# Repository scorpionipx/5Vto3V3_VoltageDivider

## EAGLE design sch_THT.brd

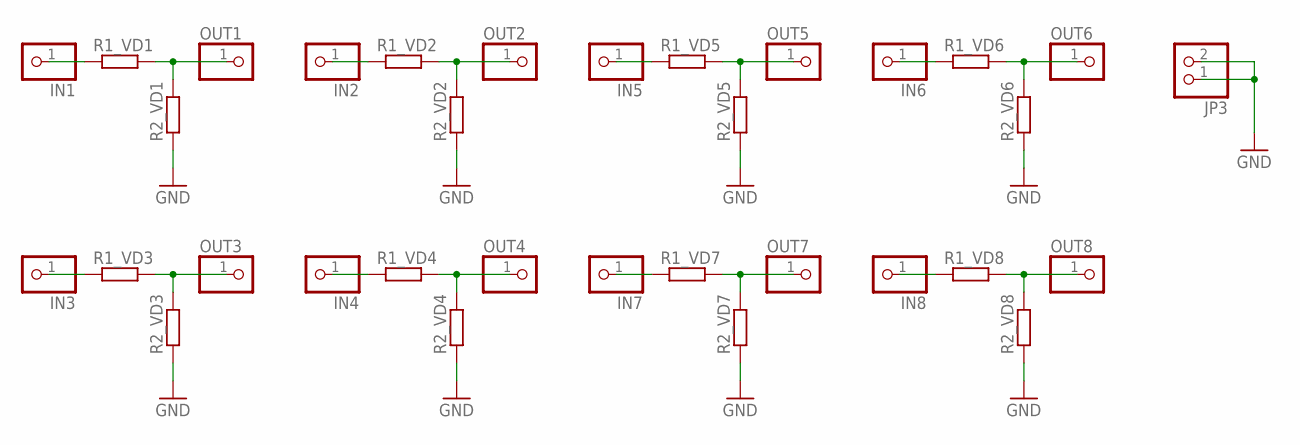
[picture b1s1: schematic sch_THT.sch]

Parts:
IN1, IN2, IN3, IN4, IN5, IN6, IN7, IN8: PINHD-1X1; 1X01
JP3: PINHD-1X2; 1X02
OUT1, OUT2, OUT3, OUT4, OUT5, OUT6, OUT7, OUT8: PINHD-1X1; 1X01
R1_VD1, R1_VD2, R1_VD3, R1_VD4, R1_VD5, R1_VD6, R1_VD7, R1_VD8, R2_VD1, R2_VD2, R2_VD3, R2_VD4, R2_VD5, R2_VD6, R2_VD7, R2_VD8: R-EU_0204/7; 0204/7

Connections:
GND: JP3.1, JP3.2, R2_VD1.1, R2_VD2.1, R2_VD3.1, R2_VD4.1, R2_VD5.1, R2_VD6.1, R2_VD7.1, R2_VD8.1
unnamed: IN1.1, R1_VD1.1
unnamed: OUT1.1, R1_VD1.2, R2_VD1.2
unnamed: IN2.1, R1_VD2.1
unnamed: OUT2.1, R1_VD2.2, R2_VD2.2
unnamed: IN3.1, R1_VD3.1
unnamed: OUT3.1, R1_VD3.2, R2_VD3.2
unnamed: IN4.1, R1_VD4.1
unnamed: OUT4.1, R1_VD4.2, R2_VD4.2
unnamed: IN5.1, R1_VD5.1
unnamed: OUT5.1, R1_VD5.2, R2_VD5.2
unnamed: IN6.1, R1_VD6.1
unnamed: OUT6.1, R1_VD6.2, R2_VD6.2
unnamed: IN7.1, R1_VD7.1
unnamed: OUT7.1, R1_VD7.2, R2_VD7.2
unnamed: IN8.1, R1_VD8.1
unnamed: OUT8.1, R1_VD8.2, R2_VD8.2

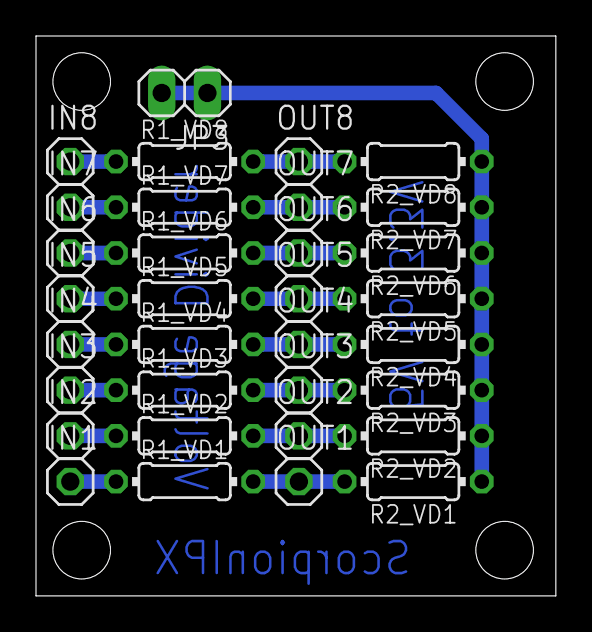
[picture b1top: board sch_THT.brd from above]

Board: 2 copper layers, 28.9 x 31.1 mm, 33 parts (0 on the bottom side), 17 nets.
